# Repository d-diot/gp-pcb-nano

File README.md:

# d-diot General Purpose Pcb Nano

This pcb is part of the [d-diot project](https://www.d-diot.com). 

Visit the dedicated [wiki page](https://wiki.d-diot.com/hardware/pcb/mysensors/gp_pcb_nano) to know more.

The [d-diot nano repeater firmware](https://github.com/d-diot/d-diot-nano-repeater) can be used with this pcb

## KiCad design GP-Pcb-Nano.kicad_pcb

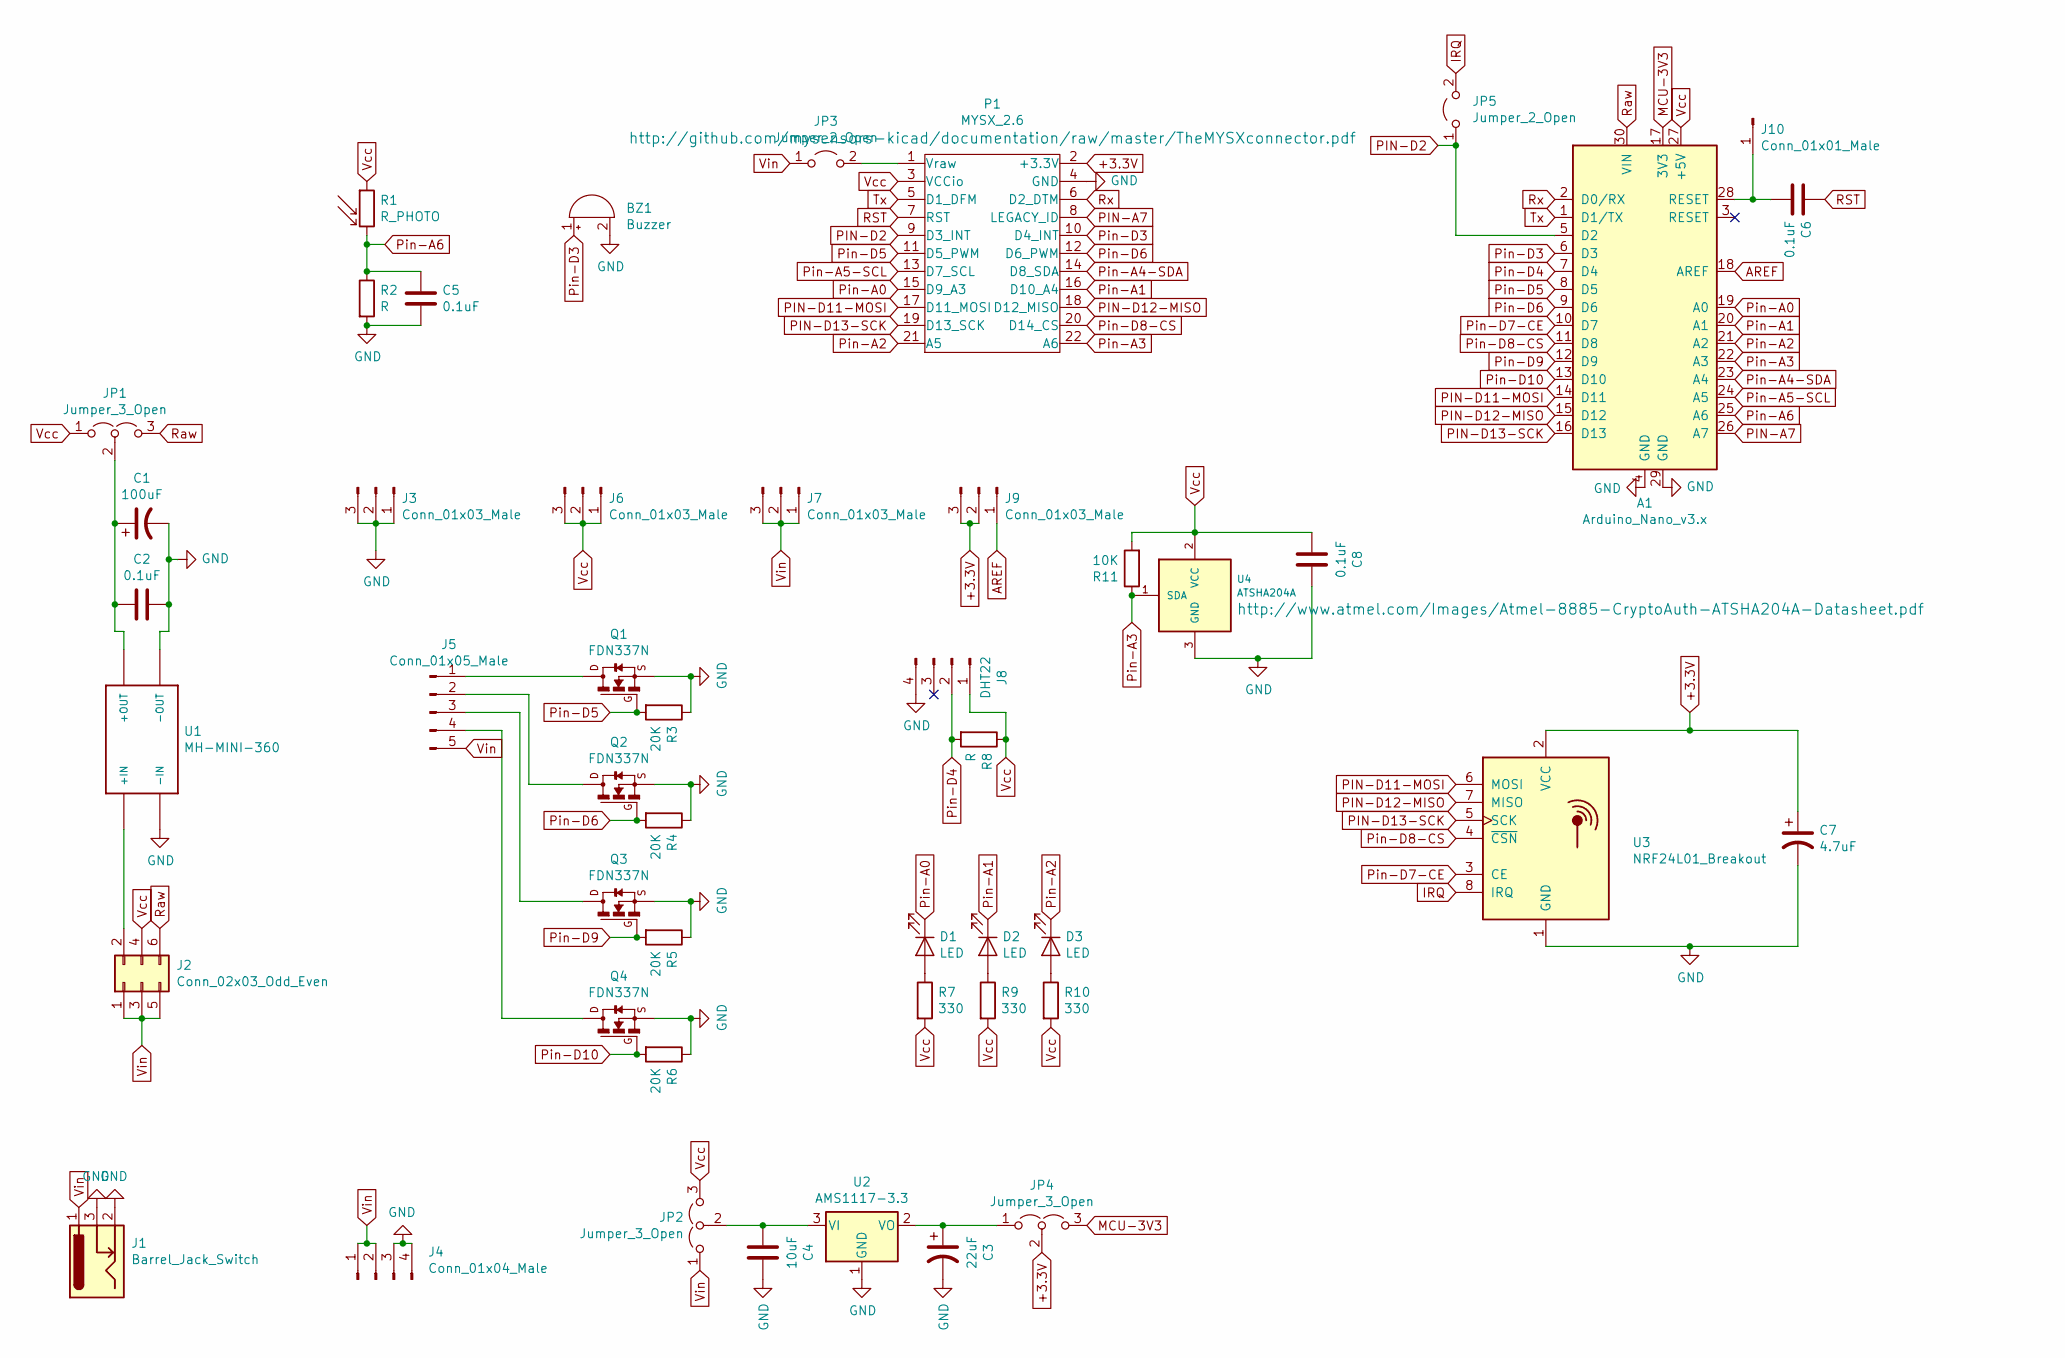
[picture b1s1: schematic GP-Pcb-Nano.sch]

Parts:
A1: Arduino_Nano_v3.x; Arduino_Nano
BZ1: Buzzer; Buzzer_12x9.5RM7.6
C1: 100uF; CP_Radial_D6.3mm_P2.50mm
C2, C5, C6, C8: 0.1uF; C_Disc_D5.1mm_W3.2mm_P5.00mm
C3: 22uF; CP_Radial_Tantal_D5.5mm_P2.50mm
C4: 10uF; C_Disc_D5.1mm_W3.2mm_P5.00mm
C7: 4.7uF; CP_Radial_D5.0mm_P2.00mm
D1, D2, D3: LED; LED_D5.0mm
J1: Barrel_Jack_Switch; BarrelJack_Wuerth_6941xx301002
J2: Conn_02x03_Odd_Even; PinHeader_2x03_P2.54mm_Vertical
J3, J6, J7, J9: Conn_01x03_Male; PinHeader_1x03_P2.54mm_Vertical
J4: Conn_01x04_Male; PinHeader_1x04_P2.54mm_Vertical
J5: Conn_01x05_Male; PinHeader_1x05_P2.54mm_Vertical
J8: DHT22; PinHeader_1x04_P2.54mm_Vertical
J10: Conn_01x01_Male; PinHeader_1x01_P2.54mm_Vertical
JP1, JP2, JP4: Jumper_3_Open; PinHeader_1x03_P2.54mm_Vertical
JP3, JP5: Jumper_2_Open; PinHeader_1x02_P2.54mm_Vertical
P1: MYSX_2.6; MYSX_2.6_SOCKET
Q1, Q2, Q3, Q4: FDN337N; SSOT-3
R1: R_PHOTO; R_LDR_5.0x4.1mm_P3mm_Vertical
R2, R8: R; R_Axial_DIN0207_L6.3mm_D2.5mm_P7.62mm_Horizontal
R3, R4, R5, R6: 20K; R_Axial_DIN0207_L6.3mm_D2.5mm_P7.62mm_Horizontal
R7, R9, R10: 330; R_Axial_DIN0207_L6.3mm_D2.5mm_P7.62mm_Horizontal
R11: 10K; R_Axial_DIN0207_L6.3mm_D2.5mm_P7.62mm_Horizontal
U1: MH-MINI-360
U2: AMS1117-3.3; SOT-223-3_TabPin2
U3: NRF24L01_Breakout; nRF24L01_Breakout
U4: ATSHA204A; SOT-23_Handsoldering

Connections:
+3.3V: C7.1, J9.2, J9.3, JP4.2 (C), P1.2 (+3.3V), U3.2 (VCC)
AREF: A1.18 (AREF), J9.1
GND: A1.4 (GND), A1.29 (GND), BZ1.2 (+), C1.2, C2.1, C3.2, C4.1, C5.1, C7.2, C8.1, J1.2, J1.3, J3.1, J3.2, J3.3, J4.3, J4.4, J8.4, P1.4 (GND), Q1.2 (S), Q2.2 (S), Q3.2 (S), Q4.2 (S), R2.2, R3.1, R4.1, R5.1, R6.1, U1.P$1 (-IN), U1.P$4 (-OUT), U2.1 (GND), U3.1 (GND), U4.3 (GND)
IRQ: JP5.2 (B), U3.8 (IRQ)
MCU-3V3: A1.17 (3V3), JP4.3 (B)
unnamed: A1.28 (RESET), C6.2, J10.1
unnamed: C1.1, C2.2, JP1.2 (C), U1.P$3 (+OUT)
unnamed: C3.1, JP4.1 (A), U2.2 (VO)
unnamed: C4.2, JP2.2 (C), U2.3 (VI)
unnamed: D1.2 (A), R7.1
unnamed: D2.2 (A), R9.1
unnamed: D3.2 (A), R10.1
unnamed: J2.2, U1.P$2 (+IN)
unnamed: J5.1, Q1.3 (D)
unnamed: J5.2, Q2.3 (D)
unnamed: J5.3, Q3.3 (D)
unnamed: J5.4, Q4.3 (D)
unnamed: JP3.2 (B), P1.1 (Vraw)
PIN-A7: A1.26 (A7), P1.8 (LEGACY_ID)
PIN-D2: A1.5 (D2), JP5.1 (A), P1.9 (D3_INT)
PIN-D11-MOSI: A1.14 (D11), P1.17 (D11_MOSI), U3.6 (MOSI)
PIN-D12-MISO: A1.15 (D12), P1.18 (D12_MISO), U3.7 (MISO)
PIN-D13-SCK: A1.16 (D13), P1.19 (D13_SCK), U3.5 (SCK)
Pin-A0: A1.19 (A0), D1.1 (K), P1.15 (D9_A3)
Pin-A1: A1.20 (A1), D2.1 (K), P1.16 (D10_A4)
Pin-A2: A1.21 (A2), D3.1 (K), P1.21 (A5)
Pin-A3: A1.22 (A3), P1.22 (A6), R11.1, U4.1 (SDA)
Pin-A4-SDA: A1.23 (A4), P1.14 (D8_SDA)
Pin-A5-SCL: A1.24 (A5), P1.13 (D7_SCL)
Pin-A6: A1.25 (A6), C5.2, R1.2, R2.1
Pin-D3: A1.6 (D3), BZ1.1 (-), P1.10 (D4_INT)
Pin-D4: A1.7 (D4), J8.2, R8.2
Pin-D5: A1.8 (D5), P1.11 (D5_PWM), Q1.1 (G), R3.2
Pin-D6: A1.9 (D6), P1.12 (D6_PWM), Q2.1 (G), R4.2
Pin-D7-CE: A1.10 (D7), U3.3 (CE)
Pin-D8-CS: A1.11 (D8), P1.20 (D14_CS), U3.4 (~CSN)
Pin-D9: A1.12 (D9), Q3.1 (G), R5.2
Pin-D10: A1.13 (D10), Q4.1 (G), R6.2
RST: C6.1, P1.7 (RST)
Raw: A1.30 (VIN), J2.6, JP1.3 (B)
Rx: A1.2 (D0/RX), P1.6 (D2_DTM)
Tx: A1.1 (D1/TX), P1.5 (D1_DFM)
Vcc: A1.27 (+5V), C8.2, J2.4, J6.1, J6.2, J6.3, J8.1, JP1.1 (A), JP2.3 (B), P1.3 (VCCio), R1.1, R7.2, R8.1, R9.2, R10.2, R11.2, U4.2 (VCC)
Vin: J1.1, J2.1, J2.3, J2.5, J4.1, J4.2, J5.5, J7.1, J7.2, J7.3, JP2.1 (A), JP3.1 (A)

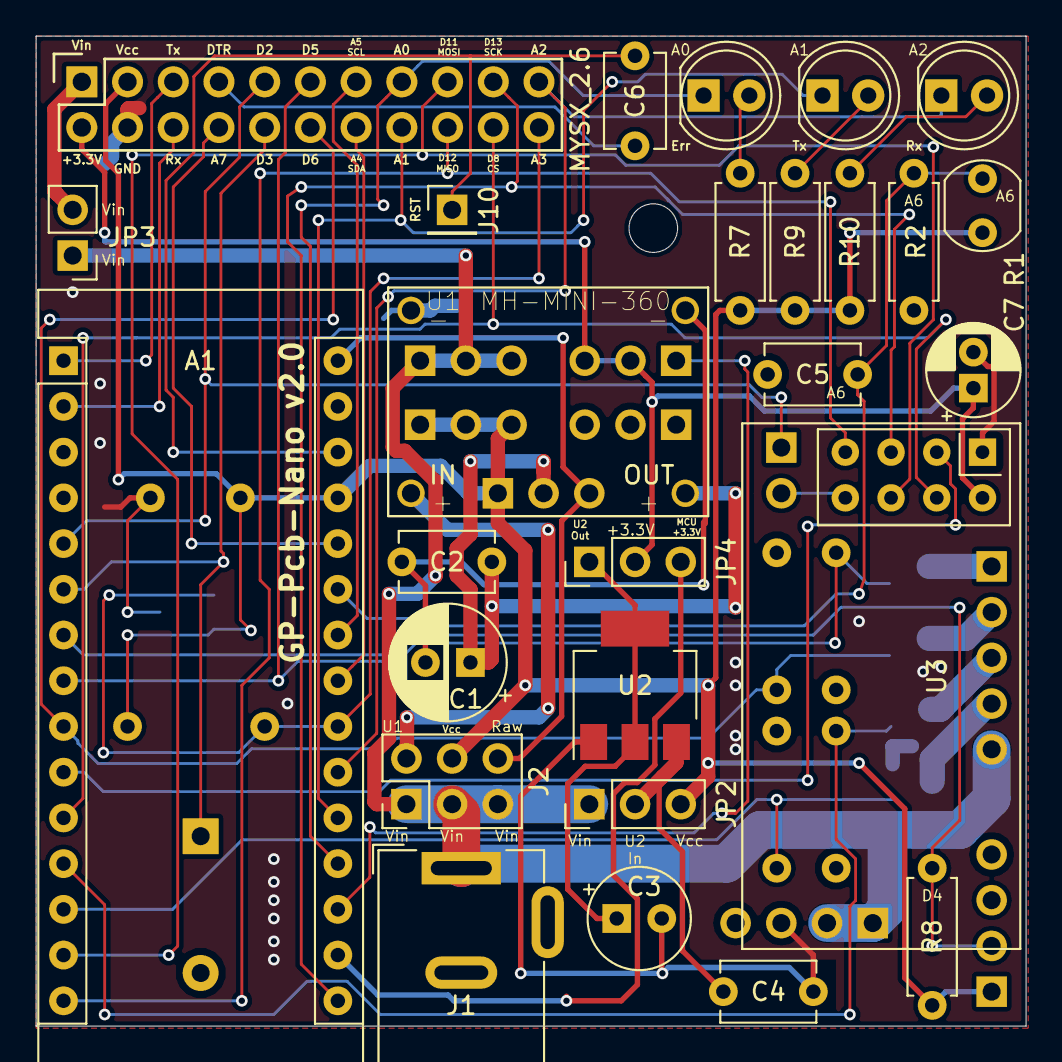
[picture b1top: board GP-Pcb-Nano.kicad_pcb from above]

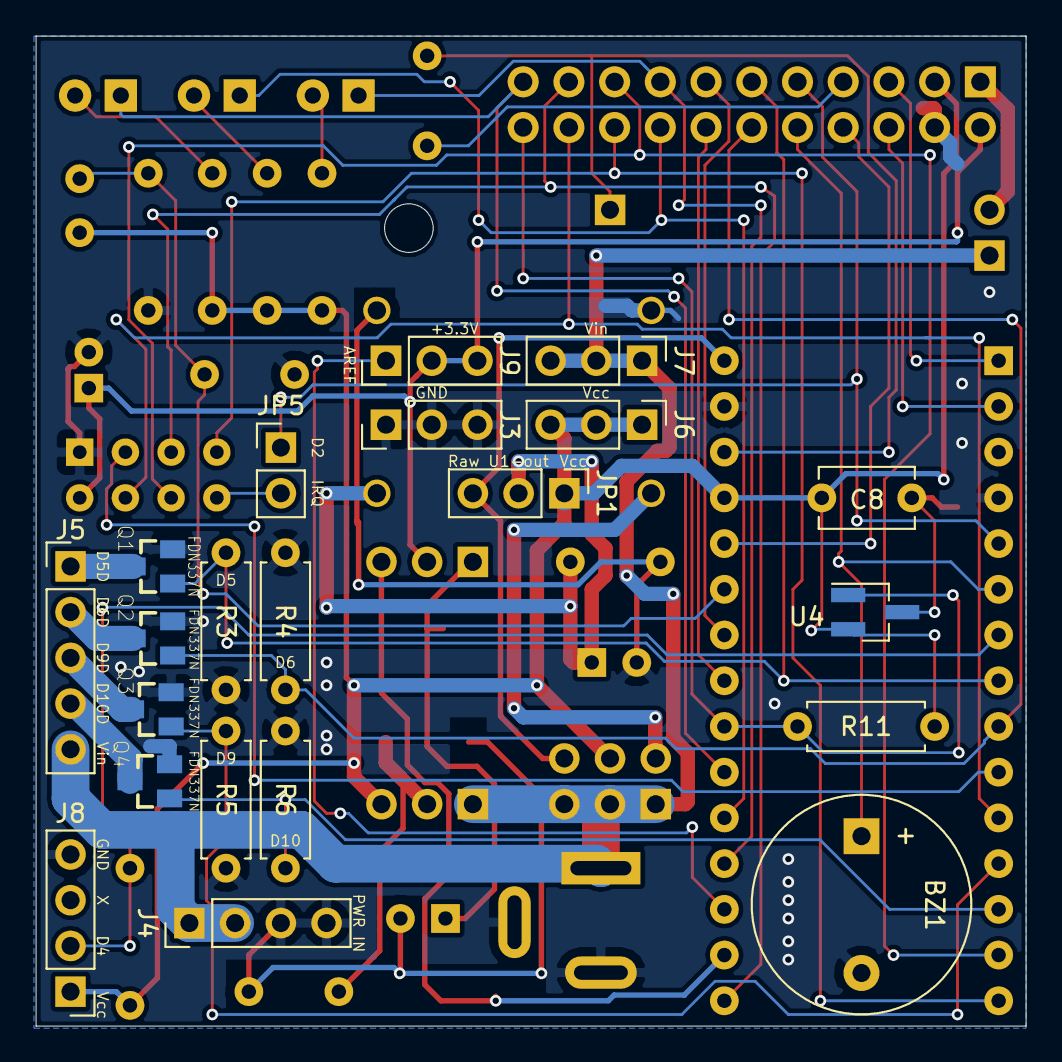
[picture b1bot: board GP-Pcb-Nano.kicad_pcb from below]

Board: 2 copper layers, 55.0 x 55.0 mm, 48 parts (22 on the bottom side), 44 nets.

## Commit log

2019-06-30 GP Pcb v.2.0
2019-06-30 GP Pcb Nano v.2.0
